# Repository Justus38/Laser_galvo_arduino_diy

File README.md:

# Laser_galvo_arduino_diy
In this project iam using arduino or similar microcontroller to control a laser galvo. Not a stepper motor laser galvo instead a real galvo with real galvo motors

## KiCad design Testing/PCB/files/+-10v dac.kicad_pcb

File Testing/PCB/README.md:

this pcb is just for testing purposes 

i forgot one gnd on the first revision that is why there is the small green wire

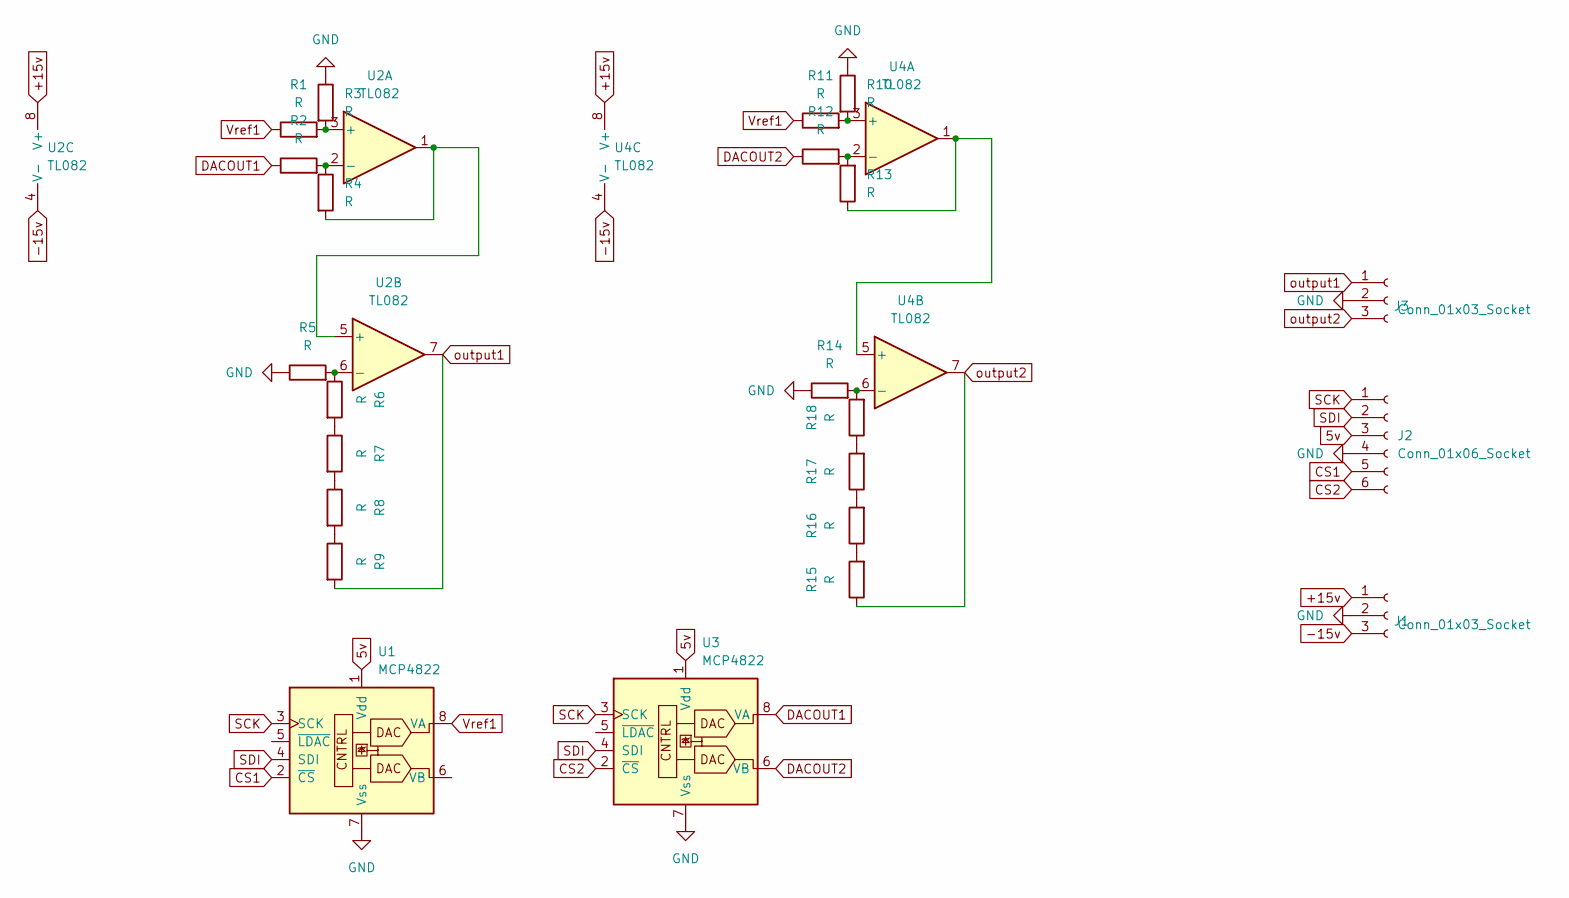
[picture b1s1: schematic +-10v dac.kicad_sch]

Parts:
J1, J3: Conn_01x03_Socket; PinHeader_1x03_P2.54mm_Vertical
J2: Conn_01x06_Socket; PinHeader_1x06_P2.54mm_Vertical
R1, R2, R3, R4, R5, R6, R7, R8, R9, R10, R11, R12, R13, R14, R15, R16, R17, R18: R; R_1206_3216Metric_Pad1.30x1.75mm_HandSolder
U1, U3: MCP4822; DIP-8_W7.62mm
U2: TL082
U4: TL082; DIP-8_W7.62mm

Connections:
5v: J2.3, U1.1 (Vdd), U3.1 (Vdd)
+15v: J1.1, U2.8 (V+), U4.8 (V+)
-15v: J1.3, U2.4 (V-), U4.4 (V-)
CS1: J2.5, U1.2 (~CS)
CS2: J2.6, U3.2 (~CS)
DACOUT1: R2.1, U3.8 (VA)
DACOUT2: R12.1, U3.6 (VB)
GND: J1.2, J2.4, J3.2, R3.1, R5.1, R10.1, R14.1, U1.7 (Vss), U3.7 (Vss)
unnamed: R6.2, R7.1
unnamed: R7.2, R8.1
unnamed: R8.2, R9.1
unnamed: R15.2, R16.1
unnamed: R16.2, R17.1
unnamed: R17.2, R18.1
unnamed: R1.2, R3.2, U2.3 (+)
unnamed: R2.2, R4.1, U2.2 (-)
unnamed: R4.2, U2.1, U2.5 (+)
unnamed: R5.2, R6.1, U2.6 (-)
unnamed: R10.2, R11.2, U4.3 (+)
unnamed: R12.2, R13.2, U4.2 (-)
unnamed: R13.1, U4.1, U4.5 (+)
unnamed: R14.2, R18.2, U4.6 (-)
SCK: J2.1, U1.3 (SCK), U3.3 (SCK)
SDI: J2.2, U1.4 (SDI), U3.4 (SDI)
Vref1: R1.1, R11.1, U1.8 (VA)
output1: J3.1, R9.2, U2.7
output2: J3.3, R15.1, U4.7

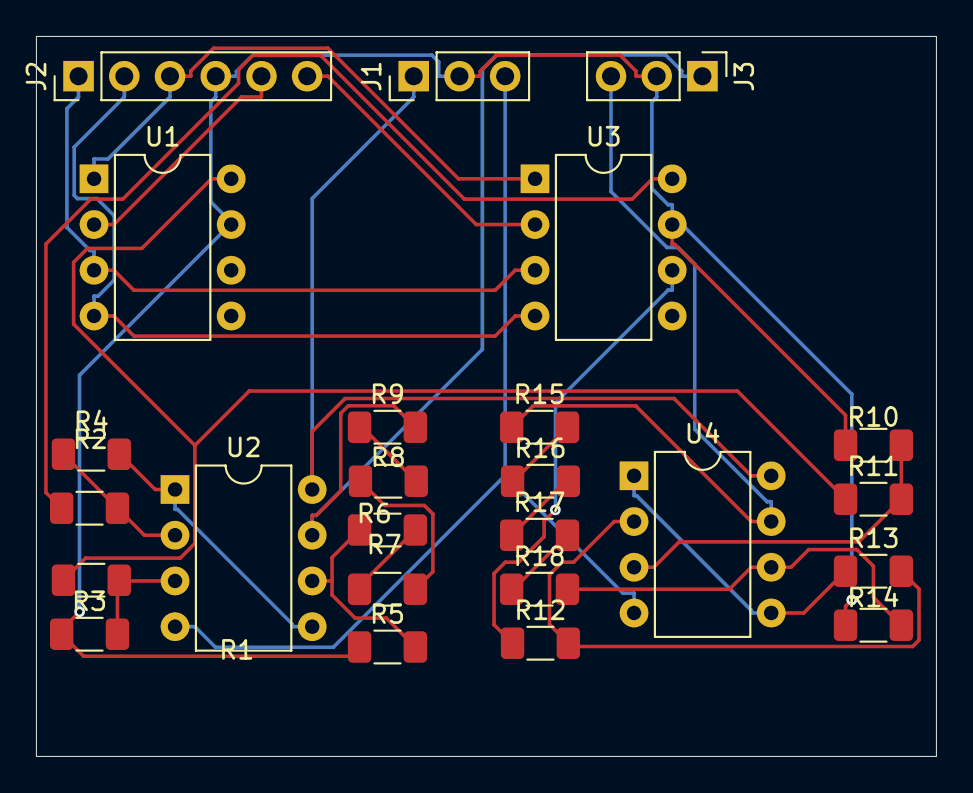
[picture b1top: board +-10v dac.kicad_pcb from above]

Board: 2 copper layers, 50.0 x 40.0 mm, 25 parts (0 on the bottom side), 27 nets.

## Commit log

2024-11-23 Create D
2024-12-08 Rename read.me to README.md
